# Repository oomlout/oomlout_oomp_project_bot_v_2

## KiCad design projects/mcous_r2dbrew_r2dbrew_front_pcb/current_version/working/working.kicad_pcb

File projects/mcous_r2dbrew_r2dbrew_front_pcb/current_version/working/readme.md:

# r2dbrew
 
## summary 
* id: mcous_r2dbrew_r2dbrew_front_pcb
* user: mcous
* name: r2dbrew
* board: r2dbrew_front_pcb
* repo: https://github.com/mcous/r2dbrew
* src_file_repo_kicad_pcb: pcb/r2dbrew-front-pcb/r2dbrew-front-pcb.kicad_pcb
* src_file_repo_kicad_pcb_link: https://github.com/mcous/r2dbrew/tree/master/pcb/r2dbrew-front-pcb/r2dbrew-front-pcb.kicad_pcb

* src_file_repo_sch: pcb/r2dbrew-front-pcb/r2dbrew-front-pcb.sch
* src_file_repo_sch_link: https://github.com/mcous/r2dbrew/tree/master/pcb/r2dbrew-front-pcb/r2dbrew-front-pcb.sch
* full details link: https://github.com/oomlout/oomlout_oomp_project_bot_v_2/tree/main/projects/mcous_r2dbrew_r2dbrew_front_pcb/current_version/working

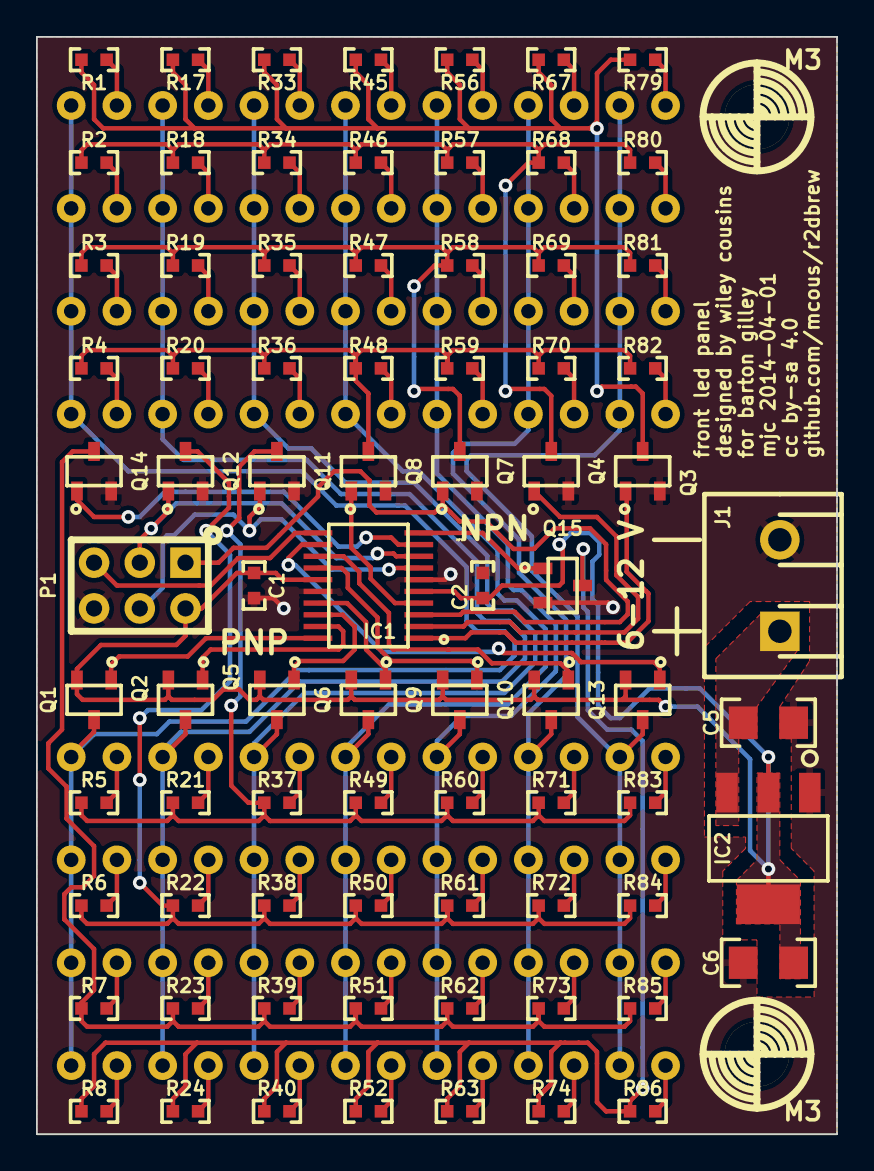
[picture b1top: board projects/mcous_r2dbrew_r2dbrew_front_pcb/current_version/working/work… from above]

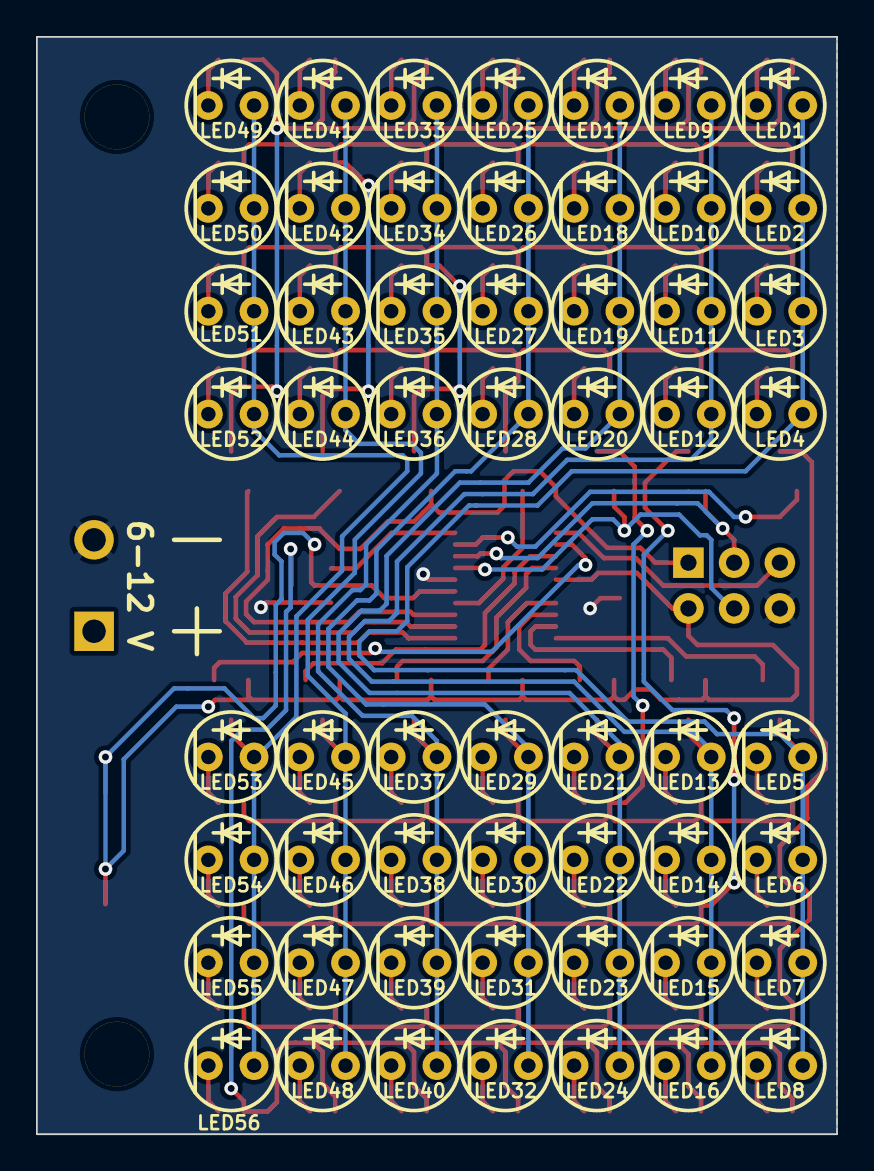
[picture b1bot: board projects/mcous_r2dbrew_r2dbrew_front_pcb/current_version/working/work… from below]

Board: 2 copper layers, 44.5 x 61.0 mm, 137 parts (56 on the bottom side), 90 nets.

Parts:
C1, C2: 0.1uF; 0603(1608m)
C5: 10uF; 1206(3216m)
C6: 22uF; 1206(3216m)
IC1: ATTINY167; TSSOP20
IC2: LM1117; SOT223
J1: 6-12V; 1x2-SCREW-TERM_P200mil
LED1, LED2, LED3, LED4, LED5, LED6, LED7, LED8, LED9, LED10, LED11, LED12, LED13, LED14, LED15, LED16, LED17, LED18, LED19, LED20, LED21, LED22, LED23, LED24, LED25, LED26, LED27, LED28, LED29, LED30, LED31, LED32, LED33, LED34, LED35, LED36, LED37, LED38, LED39, LED40, LED41, LED42, LED43, LED44, LED45, LED46, LED47, LED48, LED49, LED50, LED51, LED52, LED53, LED54, LED55, LED56: LED; 5mm-THRU-LED
M3, M3#2: VAL**; M3
P1: AVR_ISP; 2x3-ARRAY_P100mil
Q1, Q2, Q5, Q6, Q9, Q10, Q13: DDTB113ZC; SOT23
Q3, Q4, Q7, Q8, Q11, Q12, Q14, Q15: DDTD113ZC; SOT23
R1, R2, R3, R4, R5, R6, R7, R8, R17, R18, R19, R20, R21, R22, R23, R24, R33, R34, R35, R36, R37, R38, R39, R40, R45, R46, R47, R48, R49, R50, R51, R52, R56, R57, R58, R59, R60, R61, R62, R63, R67, R68, R69, R70, R71, R72, R73, R74, R79, R80, R81, R82, R83, R84, R85, R86: 68Ω; 0603(1608m)

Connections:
/AVR_RST: IC1.11, P1.5
/beer2d2 front LED panel/AVR_C0: IC1.20, Q1.1
/beer2d2 front LED panel/AVR_C1: IC1.19, Q2.1
/beer2d2 front LED panel/AVR_C2: IC1.18, Q5.1
/beer2d2 front LED panel/AVR_C3: IC1.17, Q6.1
/beer2d2 front LED panel/AVR_C4: IC1.14, Q9.1
/beer2d2 front LED panel/AVR_C5: IC1.13, Q10.1
/beer2d2 front LED panel/AVR_C6: IC1.12, Q13.1
/beer2d2 front LED panel/AVR_R0: IC1.1, Q3.1
/beer2d2 front LED panel/AVR_R1: IC1.2, Q4.1
/beer2d2 front LED panel/AVR_R2: IC1.3, P1.1, Q7.1
/beer2d2 front LED panel/AVR_R3: IC1.4, Q8.1
/beer2d2 front LED panel/AVR_R4: IC1.7, P1.4, Q11.1
/beer2d2 front LED panel/AVR_R5: IC1.8, P1.3, Q12.1
/beer2d2 front LED panel/AVR_R6: IC1.9, Q14.1
/beer2d2 front LED panel/AVR_R7: IC1.10, Q15.1
/beer2d2 front LED panel/COL0: LED1.2, LED2.2, LED3.2, LED4.2, LED5.2, LED6.2, LED7.2, LED8.2, Q1.3
/beer2d2 front LED panel/COL1: LED9.2, LED10.2, LED11.2, LED12.2, LED13.2, LED14.2, LED15.2, LED16.2, Q2.3
/beer2d2 front LED panel/COL2: LED17.2, LED18.2, LED19.2, LED20.2, LED21.2, LED22.2, LED23.2, LED24.2, Q5.3
/beer2d2 front LED panel/COL3: LED25.2, LED26.2, LED27.2, LED28.2, LED29.2, LED30.2, LED31.2, LED32.2, Q6.3
/beer2d2 front LED panel/COL4: LED33.2, LED34.2, LED35.2, LED36.2, LED37.2, LED38.2, LED39.2, LED40.2, Q9.3
/beer2d2 front LED panel/COL5: LED41.2, LED42.2, LED43.2, LED44.2, LED45.2, LED46.2, LED47.2, LED48.2, Q10.3
/beer2d2 front LED panel/COL6: LED49.2, LED50.2, LED51.2, LED52.2, LED53.2, LED54.2, LED55.2, LED56.2, Q13.3
/beer2d2 front LED panel/ROW0: Q3.3, R1.2, R17.2, R33.2, R45.2, R56.2, R67.2, R79.2
/beer2d2 front LED panel/ROW1: Q4.3, R2.2, R18.2, R34.2, R46.2, R57.2, R68.2, R80.2
/beer2d2 front LED panel/ROW2: Q7.3, R3.2, R19.2, R35.2, R47.2, R58.2, R69.2, R81.2
/beer2d2 front LED panel/ROW3: Q8.3, R4.2, R20.2, R36.2, R48.2, R59.2, R70.2, R82.2
/beer2d2 front LED panel/ROW4: Q11.3, R5.2, R21.2, R37.2, R49.2, R60.2, R71.2, R83.2
/beer2d2 front LED panel/ROW5: Q12.3, R6.2, R22.2, R38.2, R50.2, R61.2, R72.2, R84.2
/beer2d2 front LED panel/ROW6: Q14.3, R7.2, R23.2, R39.2, R51.2, R62.2, R73.2, R85.2
/beer2d2 front LED panel/ROW7: Q15.3, R8.2, R24.2, R40.2, R52.2, R63.2, R74.2, R86.2
GND: C1.1, C2.1, C5.2, C6.2, IC1.6, IC1.16, IC2.1, J1.2, P1.6, Q3.2, Q4.2, Q7.2, Q8.2, Q11.2, Q12.2, Q14.2, Q15.2
unnamed: C5.1, IC2.3, J1.1
unnamed: LED1.1, R1.1
unnamed: LED2.1, R2.1
unnamed: LED3.1, R3.1
unnamed: LED4.1, R4.1
unnamed: LED5.1, R5.1
unnamed: LED6.1, R6.1
unnamed: LED7.1, R7.1
unnamed: LED8.1, R8.1
unnamed: LED9.1, R17.1
unnamed: LED10.1, R18.1
unnamed: LED11.1, R19.1
unnamed: LED12.1, R20.1
unnamed: LED13.1, R21.1
unnamed: LED14.1, R22.1
unnamed: LED15.1, R23.1
unnamed: LED16.1, R24.1
unnamed: LED17.1, R33.1
unnamed: LED18.1, R34.1
unnamed: LED19.1, R35.1
unnamed: LED20.1, R36.1
unnamed: LED21.1, R37.1
unnamed: LED22.1, R38.1
unnamed: LED23.1, R39.1
unnamed: LED24.1, R40.1
unnamed: LED25.1, R45.1
unnamed: LED26.1, R46.1
unnamed: LED27.1, R47.1
unnamed: LED28.1, R48.1
unnamed: LED29.1, R49.1
unnamed: LED30.1, R50.1
unnamed: LED31.1, R51.1
unnamed: LED32.1, R52.1
unnamed: LED33.1, R56.1
unnamed: LED34.1, R57.1
unnamed: LED35.1, R58.1
unnamed: LED36.1, R59.1
unnamed: LED37.1, R60.1
unnamed: LED38.1, R61.1
unnamed: LED39.1, R62.1
unnamed: LED40.1, R63.1
unnamed: LED41.1, R67.1
unnamed: LED42.1, R68.1
unnamed: LED43.1, R69.1
unnamed: LED44.1, R70.1
unnamed: LED45.1, R71.1
unnamed: LED46.1, R72.1
unnamed: LED47.1, R73.1
unnamed: LED48.1, R74.1
unnamed: LED49.1, R79.1
unnamed: LED50.1, R80.1
unnamed: LED51.1, R81.1
unnamed: LED52.1, R82.1
unnamed: LED53.1, R83.1
unnamed: LED54.1, R84.1
unnamed: LED55.1, R85.1
unnamed: LED56.1, R86.1
VCC: C1.2, C2.2, C6.1, IC1.5, IC1.15, IC2.0, IC2.2, P1.2, Q1.2, Q2.2, Q5.2, Q6.2, Q9.2, Q10.2, Q13.2

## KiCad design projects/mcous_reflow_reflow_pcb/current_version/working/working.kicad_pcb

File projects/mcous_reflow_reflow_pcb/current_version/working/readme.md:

# reflow
 
## summary 
* id: mcous_reflow_reflow_pcb
* user: mcous
* name: reflow
* board: reflow_pcb
* repo: https://github.com/mcous/reflow
* src_file_repo_kicad_pcb: pcb/reflow-pcb.kicad_pcb
* src_file_repo_kicad_pcb_link: https://github.com/mcous/reflow/tree/master/pcb/reflow-pcb.kicad_pcb

* src_file_repo_sch: pcb/reflow-pcb.sch
* src_file_repo_sch_link: https://github.com/mcous/reflow/tree/master/pcb/reflow-pcb.sch
* full details link: https://github.com/oomlout/oomlout_oomp_project_bot_v_2/tree/main/projects/mcous_reflow_reflow_pcb/current_version/working

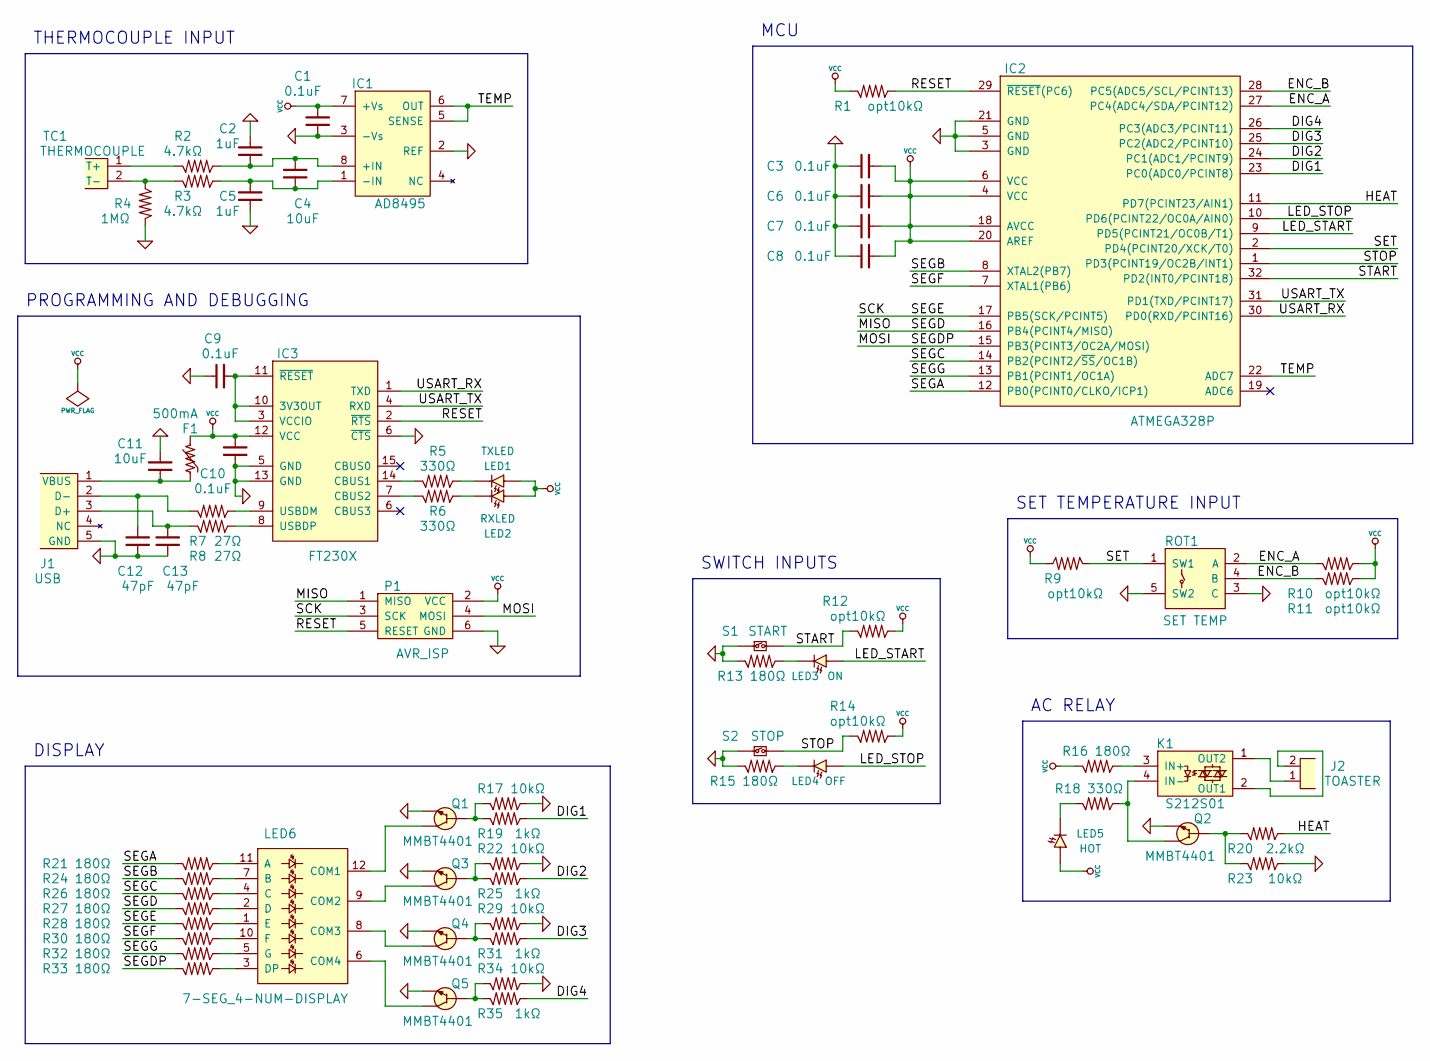
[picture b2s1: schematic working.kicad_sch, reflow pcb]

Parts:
C1, C3, C6, C7, C8, C9, C10: 0.1uF; 0603(1608m)
C2, C5: 1uF; 0603(1608m)
C4, C11: 10uF; 0603(1608m)
C12, C13: 47pF; 0603(1608m)
F1: 500mA; 1206(3216m); Part 0ZCJ0050FF2G
IC1: AD8495; MSOP8; Part AD8495ARMZ
IC2: ATMEGA328P; TQFP32_7mm; Part ATMEGA328P-AU
IC3: FT230X; SSOP16; Part FT230XS-R
J1: USB; MICROUSB_sm; Part 10118192-0001LF
J2: TOASTER; 2-PIN_SCREW-TERM_P200MIL; Part OSTTC022162
K1: S212S01; SHARP_SIP_SSR; Part S212S01F
LED1: TXLED; 0603(1608m)_led
LED2: RXLED; 0603(1608m)_led
LED3: ON; LED-5mm
LED4: OFF; LED-5mm
LED5: HOT; LED-5mm
LED6: 7-SEG_4-NUM-DISPLAY; SF_4-DIGIT_7-SEGMENT_CC; Part COM-11405
P1: AVR_ISP; 2x3-array
Q1, Q2, Q3, Q4, Q5: MMBT4401; SOT23; Part MMBT4401LT1G
R1, R9, R10, R11, R12, R14: opt10kΩ; 0603(1608m)
R2, R3: 4.7kΩ; 0603(1608m)
R4: 1MΩ; 0603(1608m)
R5, R6, R18: 330Ω; 0603(1608m)
R7, R8: 27Ω; 0603(1608m)
R13, R15, R16, R21, R24, R26, R27, R28, R30, R32, R33: 180Ω; 0603(1608m)
R17, R22, R23, R29, R34: 10kΩ; 0603(1608m)
R19, R25, R31, R35: 1kΩ; 0603(1608m)
R20: 2.2kΩ; 0603(1608m)
ROT1: SET TEMP; SF_ROTARY-ENCODER; Part RE130F-41-175F-12P
S1: START; SPST_4-pin-thru
S2: STOP; SPST_4-pin-thru
TC1: THERMOCOUPLE; THERMOCOUPLE_MINI_PCC-SMP; Part PCC-SMP-K

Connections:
/DIG1: IC2.23 (PC0(ADC0/PCINT8)), R19.2
/DIG2: IC2.24 (PC1(ADC1/PCINT9)), R25.2
/DIG3: IC2.25 (PC2(ADC2/PCINT10)), R31.2
/DIG4: IC2.26 (PC3(ADC3/PCINT11)), R35.2
/ENC_A: IC2.27 (PC4(ADC4/SDA/PCINT12)), R10.1, ROT1.2 (A)
/ENC_B: IC2.28 (PC5(ADC5/SCL/PCINT13)), R11.1, ROT1.4 (B)
/HEAT: IC2.11 (PD7(PCINT23/AIN1)), R20.2
/LED_START: IC2.9 (PD5(PCINT21/OC0B/T1)), LED3.2 (A)
/LED_STOP: IC2.10 (PD6(PCINT22/OC0A/AIN0)), LED4.2 (A)
/MISO: IC2.16 (PB4(PCINT4/MISO)), P1.1 (MISO), R27.1
/MOSI: IC2.15 (PB3(PCINT3/OC2A/MOSI)), P1.4 (MOSI), R33.1
/RESET: IC2.29 (~RESET(PC6)), IC3.2 (~RTS), P1.5 (RESET), R1.2
/SCK: IC2.17 (PB5(SCK/PCINT5)), P1.3 (SCK), R28.1
/SEGA: IC2.12 (PB0(PCINT0/CLKO/ICP1)), R21.1
/SEGB: IC2.8 (XTAL2(PB7)), R24.1
/SEGC: IC2.14 (PB2(PCINT2/~SS/OC1B)), R26.1
/SEGF: IC2.7 (XTAL1(PB6)), R30.1
/SEGG: IC2.13 (PB1(PCINT1/OC1A)), R32.1
/SET: IC2.2 (PD4(PCINT20/XCK/T0)), R9.1, ROT1.1 (SW1)
/START: IC2.32 (PD2(INT0/PCINT18)), R12.1, S1.2
/STOP: IC2.1 (PD3(PCINT19/OC2B/INT1)), R14.1, S2.2
/TEMP: IC1.5 (SENSE), IC1.6 (OUT), IC2.22 (ADC7)
/USART_RX: IC2.30 (PD0(RXD/PCINT16)), IC3.1 (TXD)
/USART_TX: IC2.31 (PD1(TXD/PCINT17)), IC3.4 (RXD)
GND: C1.1, C2.2, C3.1, C5.1, C6.1, C7.1, C8.1, C9.1, C10.1, C11.2, C12.1, C13.1, IC1.2 (REF), IC1.3 (-Vs), IC2.3 (GND), IC2.5 (GND), IC2.21 (GND), IC3.5 (GND), IC3.6 (CBUS3), IC3.13 (GND), J1.5 (GND), P1.6 (GND), Q1.2 (E), Q2.2 (E), Q3.2 (E), Q4.2 (E), Q5.2 (E), R4.1, R13.1, R15.1, R17.2, R22.2, R23.2, R29.2, R34.2, ROT1.3 (C), ROT1.5 (SW2), S1.1, S2.1; also elsewhere on the board
unnamed: LED6.11 (A), R21.2
unnamed: LED3.1 (C), R13.2
unnamed: LED4.1 (C), R15.2
unnamed: LED6.7 (B), R24.2
unnamed: LED6.4 (C), R26.2
unnamed: LED6.2 (D), R27.2
unnamed: LED6.1 (E), R28.2
unnamed: LED6.10 (F), R30.2
unnamed: LED6.5 (G), R32.2
unnamed: LED6.3 (DP), R33.2
unnamed: Q1.1 (B), R17.1, R19.1
unnamed: K1.3 (IN+), R16.2
unnamed: Q4.1 (B), R29.1, R31.1
unnamed: Q5.1 (B), R34.1, R35.1
unnamed: LED6.12 (COM1), Q1.3 (C)
unnamed: LED6.9 (COM2), Q3.3 (C)
unnamed: Q3.1 (B), R22.1, R25.1
unnamed: IC3.14 (CBUS1), R5.1
unnamed: IC3.7 (CBUS2), R6.1
unnamed: LED2.1 (C), R6.2
unnamed: IC3.8 (USBDP), R8.2
unnamed: C13.2, J1.3 (D+), R8.1
unnamed: LED1.1 (C), R5.2
unnamed: R2.1, TC1.1 (T+)
unnamed: K1.4 (IN-), Q2.3 (C), R18.2
unnamed: IC3.9 (USBDM), R7.2
unnamed: C9.2, IC3.3 (VCCIO), IC3.10 (3V3OUT), IC3.11 (~RESET)
unnamed: J2.2, K1.2 (OUT1)
unnamed: LED5.1 (C), R18.1
unnamed: J2.1, K1.1 (OUT2)
unnamed: C12.2, J1.2 (D-), R7.1
unnamed: Q2.1 (B), R20.1, R23.1
unnamed: LED6.8 (COM3), Q4.3 (C)
unnamed: LED6.6 (COM4), Q5.3 (C)
unnamed: C2.1, C4.2, IC1.8 (+IN), R2.2
unnamed: R3.1, R4.2, TC1.2 (T-)
unnamed: C4.1, C5.2, IC1.1 (-IN), R3.2
unnamed: C11.1, F1.1, J1.1 (VBUS)
VCC: C1.2, C3.2, C6.2, C7.2, C8.2, C10.2, F1.2, IC1.7 (+Vs), IC2.4 (VCC), IC2.6 (VCC), IC2.18 (AVCC), IC2.20 (AREF), IC3.12 (VCC), LED1.2 (A), LED2.2 (A), LED5.2 (A), P1.2 (VCC), R1.1, R9.2, R10.2, R11.2, R12.2, R14.2, R16.1

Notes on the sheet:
MCU
AC RELAY
SET TEMPERATURE INPUT
SWITCH INPUTS
THERMOCOUPLE INPUT
DISPLAY
PROGRAMMING AND DEBUGGING

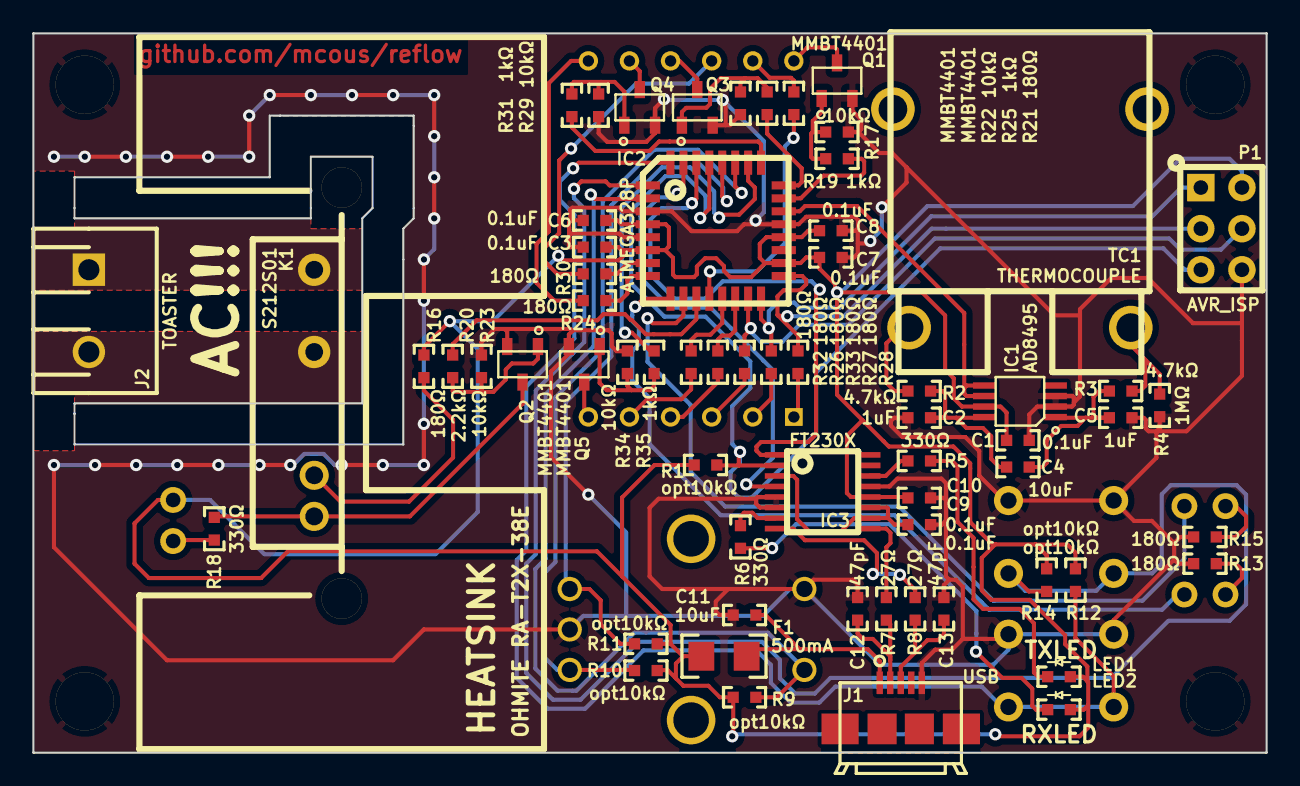
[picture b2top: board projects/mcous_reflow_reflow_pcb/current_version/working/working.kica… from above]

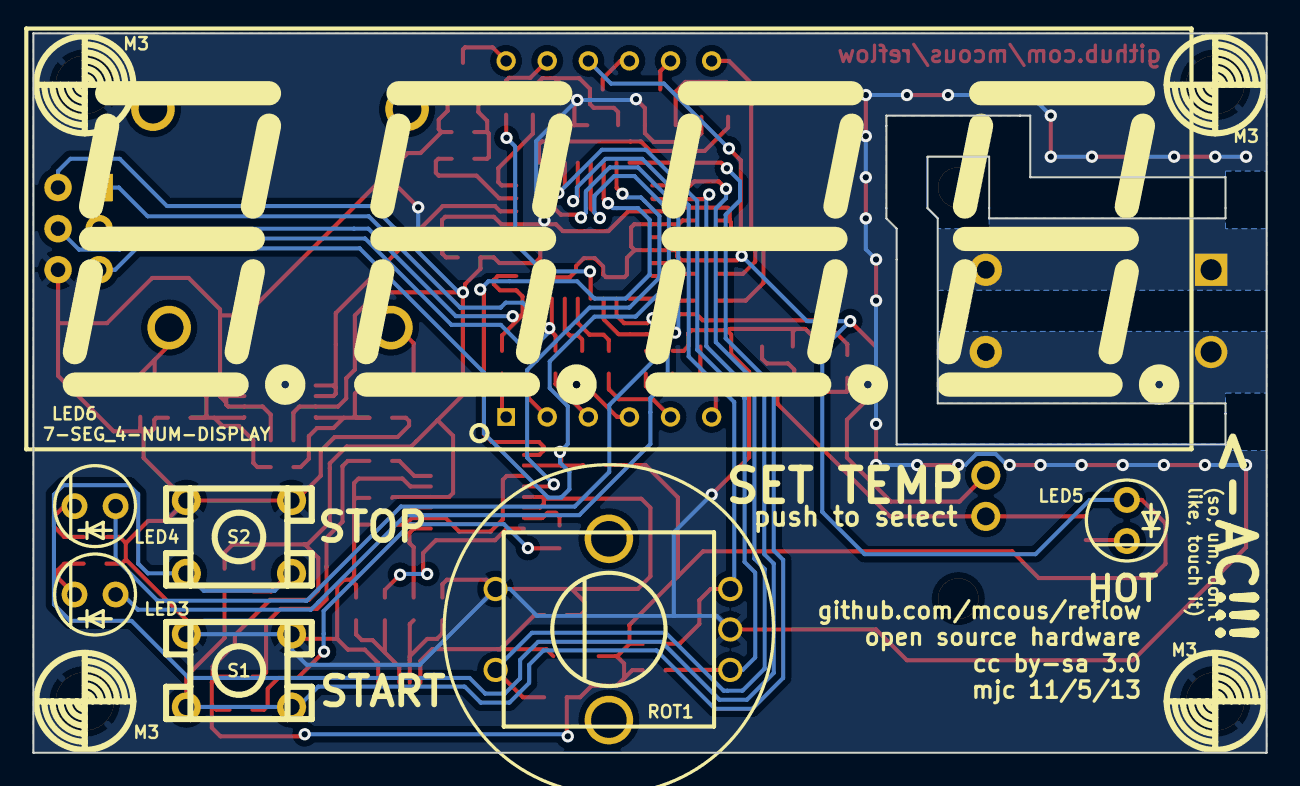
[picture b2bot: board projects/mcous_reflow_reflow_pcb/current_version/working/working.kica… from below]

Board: 2 copper layers, 76.2 x 44.5 mm, 75 parts (11 on the bottom side), 64 nets.

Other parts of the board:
M3, M3#2, M3#3, M3#4: VAL**; M3

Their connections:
GND: M3.1, M3#2.1, M3#3.1, M3#4.1; also elsewhere on the board

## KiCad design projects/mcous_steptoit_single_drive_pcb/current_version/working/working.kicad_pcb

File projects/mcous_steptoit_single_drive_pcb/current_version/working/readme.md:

# steptoit
 
## summary 
* id: mcous_steptoit_single_drive_pcb
* user: mcous
* name: steptoit
* board: single_drive_pcb
* repo: https://github.com/mcous/steptoit
* src_file_repo_kicad_pcb: single-drive_pcb/single-drive_pcb.kicad_pcb
* src_file_repo_kicad_pcb_link: https://github.com/mcous/steptoit/tree/master/single-drive_pcb/single-drive_pcb.kicad_pcb

* src_file_repo_sch: single-drive_pcb/single-drive_pcb.sch
* src_file_repo_sch_link: https://github.com/mcous/steptoit/tree/master/single-drive_pcb/single-drive_pcb.sch
* full details link: https://github.com/oomlout/oomlout_oomp_project_bot_v_2/tree/main/projects/mcous_steptoit_single_drive_pcb/current_version/working

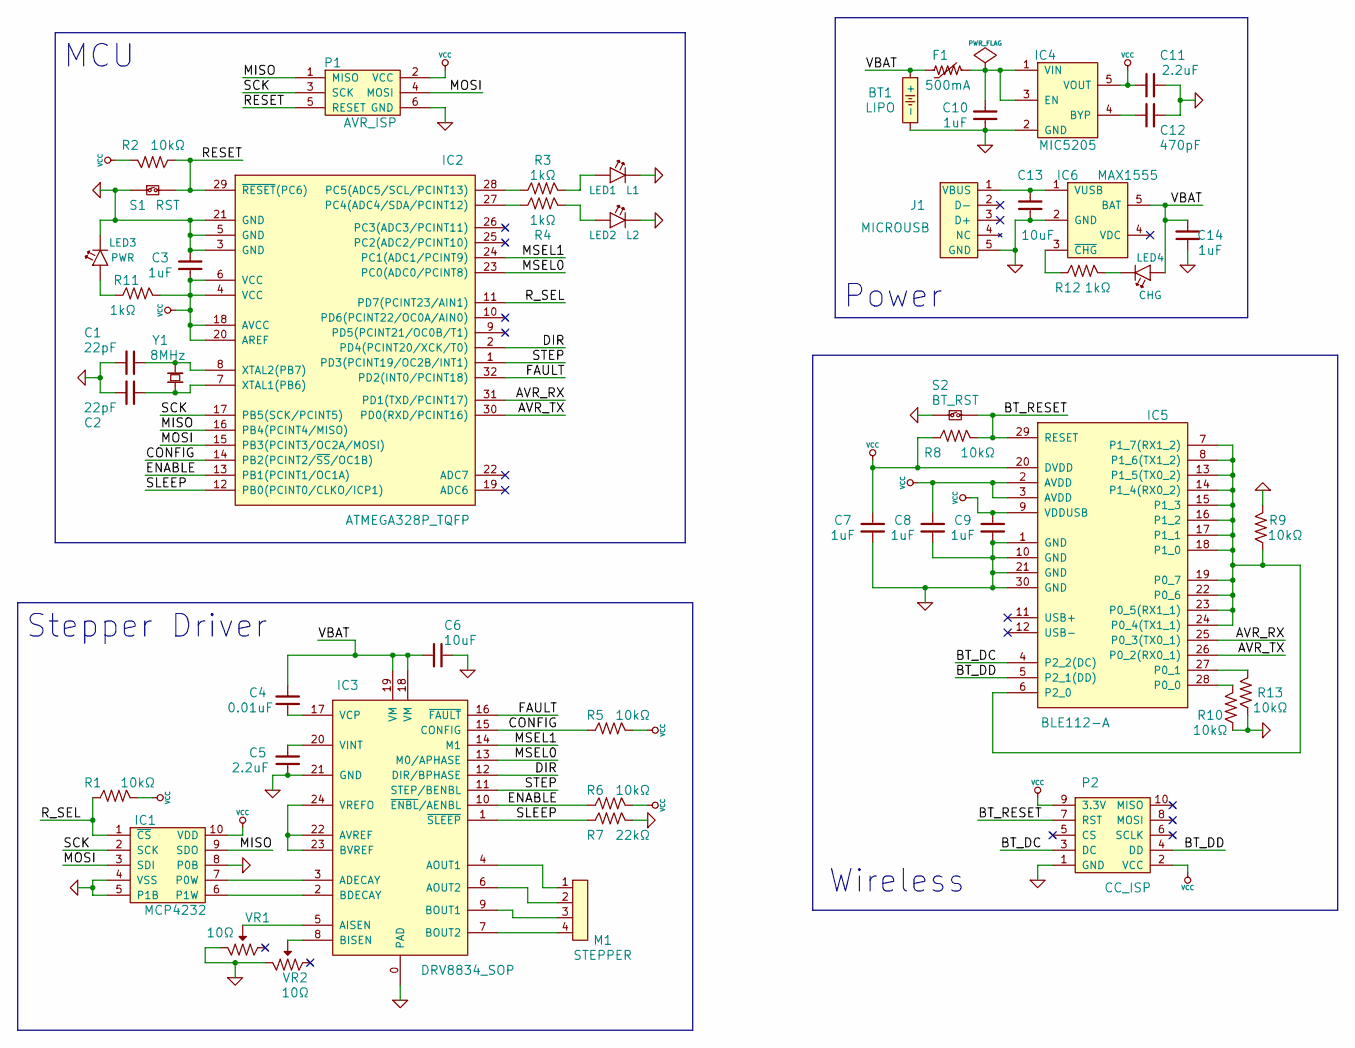
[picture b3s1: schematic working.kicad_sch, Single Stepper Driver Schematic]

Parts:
BT1: LIPO
C1, C2: 22pF
C3, C7, C8, C9, C10, C14: 1uF
C4: 0.01uF
C5, C11: 2.2uF
C6, C13: 10uF
C12: 470pF
F1: 500mA
IC1: MCP4232
IC2: ATMEGA328P_TQFP
IC3: DRV8834_SOP
IC4: MIC5205
IC5: BLE112-A
IC6: MAX1555
J1: MICROUSB
LED1: L1
LED2: L2
LED3: PWR
LED4: CHG
M1: STEPPER
P1: AVR_ISP
P2: CC_ISP
R1, R2, R5, R6, R8, R9, R10, R13: 10kΩ
R3, R4, R11, R12: 1kΩ
R7: 22kΩ
S1: RST
S2: BT_RST
VR1, VR2: 10Ω
Y1: 8MHz

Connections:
/AVR_RX: IC2.31 (PD1(TXD/PCINT17)), IC5.25 (P0_3(TX0_1))
/AVR_TX: IC2.30 (PD0(RXD/PCINT16)), IC5.26 (P0_2(RX0_1))
/BT_DC: IC5.4 (P2_2(DC)), P2.3 (DC)
/BT_DD: IC5.5 (P2_1(DD)), P2.4 (DD)
/BT_RESET: IC5.29 (RESET), P2.7 (RST), R8.2, S2.2
/CONFIG: IC2.14 (PB2(PCINT2/~SS/OC1B)), IC3.15 (CONFIG), R5.1
/DIR: IC2.2 (PD4(PCINT20/XCK/T0)), IC3.12 (DIR/BPHASE)
/ENABLE: IC2.13 (PB1(PCINT1/OC1A)), IC3.10 (~ENBL/AENBL), R6.1
/FAULT: IC2.32 (PD2(INT0/PCINT18)), IC3.16 (~FAULT)
/MISO: IC1.9 (SDO), IC2.16 (PB4(PCINT4/MISO)), P1.1 (MISO)
/MOSI: IC1.3 (SDI), IC2.15 (PB3(PCINT3/OC2A/MOSI)), P1.4 (MOSI)
/MSEL0: IC2.23 (PC0(ADC0/PCINT8)), IC3.13 (M0/APHASE)
/MSEL1: IC2.24 (PC1(ADC1/PCINT9)), IC3.14 (M1)
/RESET: IC2.29 (~RESET(PC6)), P1.5 (RESET), R2.1, S1.2
/R_SEL: IC1.1 (~CS), IC2.11 (PD7(PCINT23/AIN1)), R1.1
/SCK: IC1.2 (SCK), IC2.17 (PB5(SCK/PCINT5)), P1.3 (SCK)
/SLEEP: IC2.12 (PB0(PCINT0/CLKO/ICP1)), IC3.1 (~SLEEP), R7.1
/STEP: IC2.1 (PD3(PCINT19/OC2B/INT1)), IC3.11 (STEP/BENBL)
/VBAT: BT1.1 (+), C4.1, C6.1, C14.2, F1.1, IC3.18 (VM), IC3.19 (VM), IC6.5 (BAT), LED4.2 (A)
GND: BT1.2 (-), C1.2, C2.1, C3.2, C5.1, C6.2, C7.1, C8.1, C9.1, C10.1, C11.2, C12.2, C13.1, C14.1, IC1.4 (VSS), IC1.5 (P1B), IC1.8 (P0B), IC2.3 (GND), IC2.5 (GND), IC2.21 (GND), IC3.0 (PAD), IC3.21 (GND), IC4.2 (GND), IC5.1 (GND), IC5.10 (GND), IC5.21 (GND), IC5.30 (GND), IC6.2 (GND), J1.5 (GND), LED1.1 (C), LED2.1 (C), LED3.1 (C), P1.6 (GND), P2.1 (GND), R7.2, R9.2, R10.1, R13.1, S1.1, S2.1, VR1.3 (E2), VR2.3 (E2)
unnamed: LED4.1 (C), R12.2
unnamed: C13.2, IC6.1 (VUSB), J1.1 (VBUS)
unnamed: IC3.7 (BOUT2), M1.4
unnamed: C10.2, F1.2, IC4.1 (VIN), IC4.3 (EN)
unnamed: LED3.2 (A), R11.1
unnamed: IC3.22 (AVREF), IC3.23 (BVREF), IC3.24 (VREFO)
unnamed: IC6.3 (~CHG), R12.1
unnamed: C4.2, IC3.17 (VCP)
unnamed: C5.2, IC3.20 (VINT)
unnamed: IC3.9 (BOUT1), M1.3
unnamed: IC3.4 (AOUT1), M1.1
unnamed: C12.1, IC4.4 (BYP)
unnamed: IC5.27 (P0_1), R13.2
unnamed: IC3.6 (AOUT2), M1.2
unnamed: IC5.28 (P0_0), R10.2
unnamed: IC1.7 (P0W), IC3.3 (ADECAY)
unnamed: IC1.6 (P1W), IC3.2 (BDECAY)
unnamed: IC3.5 (AISEN), VR1.2 (W)
unnamed: IC3.8 (BISEN), VR2.2 (W)
unnamed: IC2.28 (PC5(ADC5/SCL/PCINT13)), R3.1
unnamed: IC2.27 (PC4(ADC4/SDA/PCINT12)), R4.1
unnamed: LED2.2 (A), R4.2
unnamed: LED1.2 (A), R3.2
unnamed: IC5.6 (P2_0), IC5.7 (P1_7(RX1_2)), IC5.8 (P1_6(TX1_2)), IC5.13 (P1_5(TX0_2)), IC5.14 (P1_4(RX0_2)), IC5.15 (P1_3), IC5.16 (P1_2), IC5.17 (P1_1), IC5.18 (P1_0), IC5.19 (P0_7), IC5.22 (P0_6), IC5.23 (P0_5(RX1_1)), IC5.24 (P0_4(TX1_1)), R9.1
unnamed: C1.1, IC2.8 (XTAL2(PB7)), Y1.2
unnamed: C2.2, IC2.7 (XTAL1(PB6)), Y1.1
VCC: C3.1, C7.2, C8.2, C9.2, C11.1, IC1.10 (VDD), IC2.4 (VCC), IC2.6 (VCC), IC2.18 (AVCC), IC2.20 (AREF), IC4.5 (VOUT), IC5.2 (AVDD), IC5.3 (AVDD), IC5.9 (VDDUSB), IC5.20 (DVDD), P1.2 (VCC), P2.2 (VCC), P2.9 (3.3V), R1.2, R2.2, R5.2, R6.2, R8.1, R11.2

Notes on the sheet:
Wireless
Power
Stepper Driver
MCU

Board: 2 copper layers, 48 parts (0 on the bottom side), 47 nets, no tracks yet.

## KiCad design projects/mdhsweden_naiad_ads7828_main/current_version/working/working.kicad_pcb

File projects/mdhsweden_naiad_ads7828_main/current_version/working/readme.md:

# naiad_ads7828
 
## summary 
* id: mdhsweden_naiad_ads7828_main
* user: mdhsweden
* name: naiad_ads7828
* board: main
* repo: https://github.com/MDHSweden/NAIAD-ADS7828
* src_file_repo_kicad_pcb: LPKF/main.kicad_pcb
* src_file_repo_kicad_pcb_link: https://github.com/MDHSweden/NAIAD-ADS7828/tree/master/LPKF/main.kicad_pcb

* src_file_repo_sch: LPKF/main.sch
* src_file_repo_sch_link: https://github.com/MDHSweden/NAIAD-ADS7828/tree/master/LPKF/main.sch
* full details link: https://github.com/oomlout/oomlout_oomp_project_bot_v_2/tree/main/projects/mdhsweden_naiad_ads7828_main/current_version/working

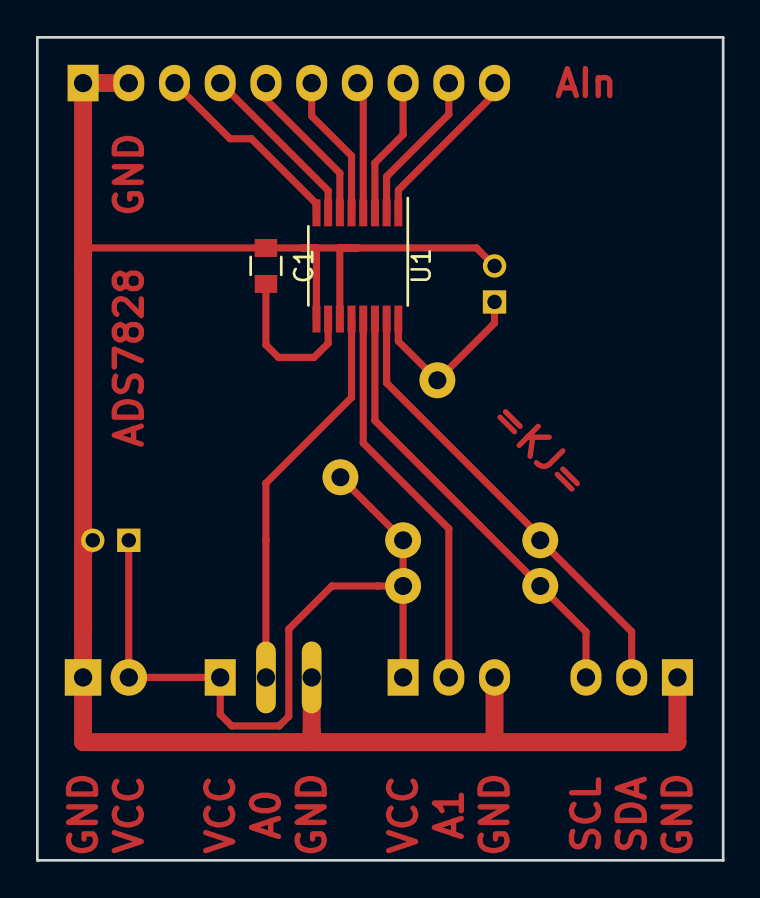
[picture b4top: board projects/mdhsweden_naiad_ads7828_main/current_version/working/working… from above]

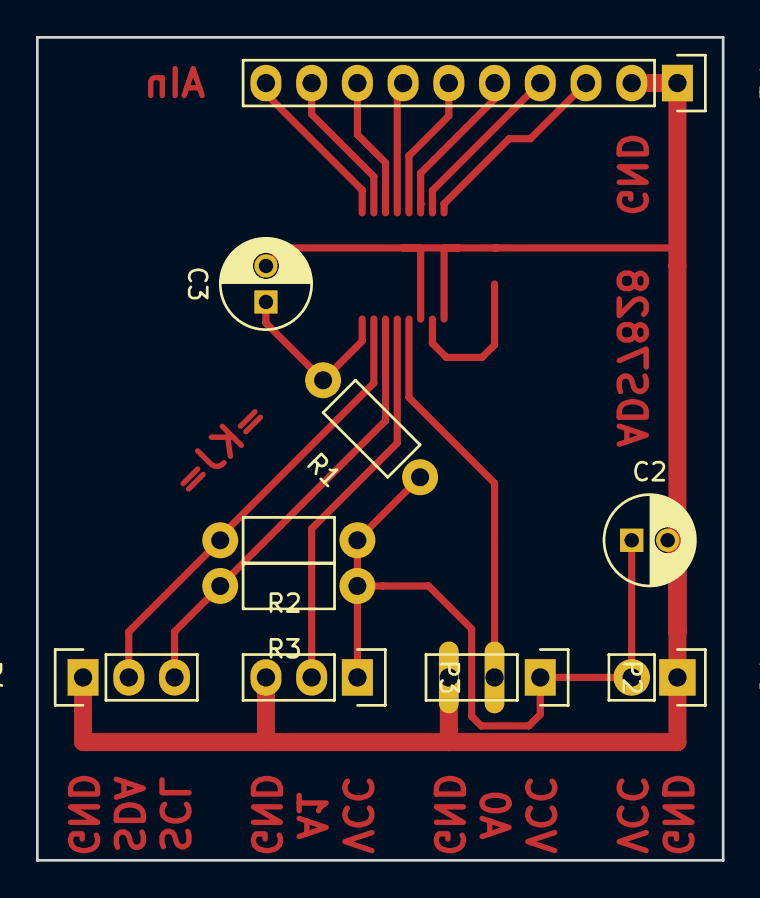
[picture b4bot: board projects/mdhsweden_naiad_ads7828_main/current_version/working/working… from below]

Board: 2 copper layers, 38.1 x 45.7 mm, 12 parts (10 on the bottom side), 16 nets.

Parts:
C1: 0.1u; C_0805
C2, C3: 10u; C_Radial_D5_L11_P2
P1: CONN_01X10; Pin_Header_Straight_1x10
P2: Address 0; Pin_Header_Straight_1x03
P3: Address 1; Pin_Header_Straight_1x03
P4: I2C Connector; Pin_Header_Straight_1x03
P5: Power Connector; Pin_Header_Straight_1x02
R1: 5; Resistor_Horizontal_RM7mm
R2, R3: 2K; Resistor_Horizontal_RM7mm
U1: ADS7828; TSSOP-16_4.4x5mm_Pitch0.65mm

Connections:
/A0: P2.2, U1.12
/A1: P3.2, U1.13
/SCL: P4.3, R3.2, U1.14
/SDA: P4.2, R2.2, U1.15
GND: C1.1, C2.2, C3.2, P1.1, P1.2, P2.3, P3.3, P4.1, P5.1, U1.9, U1.11
unnamed: C1.2, U1.10
unnamed: C3.1, R1.2, U1.16
unnamed: P1.3, U1.8
unnamed: P1.4, U1.7
unnamed: P1.5, U1.6
unnamed: P1.6, U1.5
unnamed: P1.7, U1.4
unnamed: P1.8, U1.3
unnamed: P1.9, U1.2
unnamed: P1.10, U1.1
VCC: C2.1, P2.1, P3.1, P5.2, R1.1, R2.1, R3.1

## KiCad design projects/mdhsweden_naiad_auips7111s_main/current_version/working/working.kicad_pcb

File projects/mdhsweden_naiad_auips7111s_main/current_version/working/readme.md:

# naiad_auips7111s
 
## summary 
* id: mdhsweden_naiad_auips7111s_main
* user: mdhsweden
* name: naiad_auips7111s
* board: main
* repo: https://github.com/MDHSweden/NAIAD-AUIPS7111S
* src_file_repo_kicad_pcb: p3/main.kicad_pcb
* src_file_repo_kicad_pcb_link: https://github.com/MDHSweden/NAIAD-AUIPS7111S/tree/master/p3/main.kicad_pcb

* src_file_repo_sch: p3/main.sch
* src_file_repo_sch_link: https://github.com/MDHSweden/NAIAD-AUIPS7111S/tree/master/p3/main.sch
* full details link: https://github.com/oomlout/oomlout_oomp_project_bot_v_2/tree/main/projects/mdhsweden_naiad_auips7111s_main/current_version/working

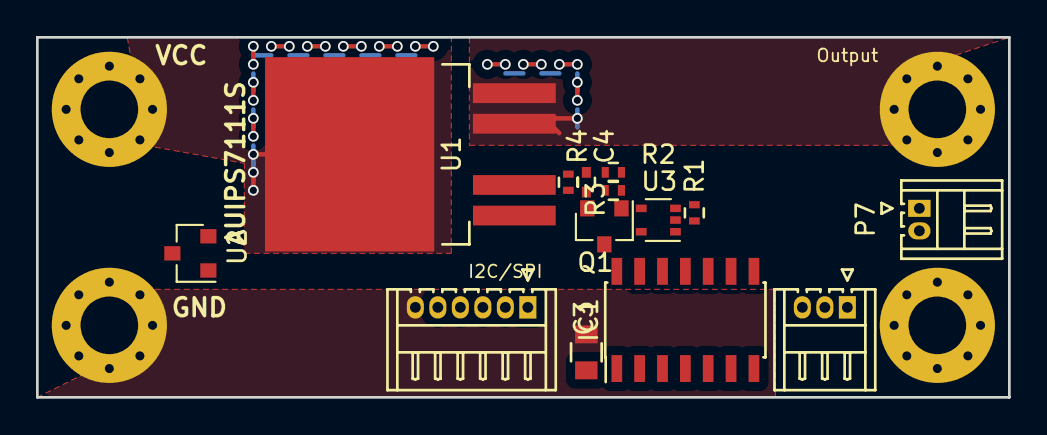
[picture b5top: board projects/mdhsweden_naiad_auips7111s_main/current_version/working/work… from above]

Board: 2 copper layers, 54.0 x 20.0 mm, 18 parts (0 on the bottom side), 15 nets.

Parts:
C3: 10uF; C_0805
C4: 1uF; C_0402
IC1: ATTINY84-S; SOIC-14_3.9x8.7mm_Pitch1.27mm
P1, P4, P5, P6: CONN_01X01; MountingHole_3.2mm_M3_Pad_Via
P2: CONN_01X06; Hirose_DF13-06P-1.25DS_06x1.25mm_Angled
P3: CONN_01X03; Hirose_DF13-03P-1.25DS_03x1.25mm_Angled
P7: CONN_01X02; Hirose_DF13-02P-1.25DS_02x1.25mm_Angled
Q1: BSS138; SOT-23
R1, R2: 4.7k; R_0402
R3: 10k; R_0402
R4: 3.3k; R_0402
U1: AUIPS7111S; TO-263-!3
U2: LM3480-5.0; SOT-23
U3: 74LVC1G08; SOT-353

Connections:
+5V: C3.1, IC1.1, P2.5, P3.2, U2.1, U3.5
/Current_Feedback: IC1.12, R3.1
/ENB1: IC1.10, U3.1
/ENB2: P3.3, R1.1, U3.2
/IN: Q1.3, U1.1
/Ifb: C4.1, R3.2, R4.1, U1.2
/MISO: IC1.8, P2.3
/Out: P5.1, U1.4, U1.5
/PWM1: IC1.5, P7.2
/RESET: IC1.4, P2.2
/SCL/SCK: IC1.9, P2.4
/SDA/MOSI: IC1.7, P2.1
GND: C3.2, C4.2, IC1.14, P2.6, P3.1, P4.1, P6.1, P7.1, Q1.2, R1.2, R2.2, R4.2, U2.3, U3.3
unnamed: Q1.1, R2.1, U3.4
VCC: P1.1, U1.3, U2.2

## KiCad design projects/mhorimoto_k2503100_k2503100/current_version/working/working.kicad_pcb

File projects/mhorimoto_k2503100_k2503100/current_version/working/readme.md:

# k2503100
 
## summary 
* id: mhorimoto_k2503100_k2503100
* user: mhorimoto
* name: k2503100
* board: k2503100
* repo: https://github.com/mhorimoto/k2503100
* src_file_repo_kicad_pcb: KiCAD/k2503100.kicad_pcb
* src_file_repo_kicad_pcb_link: https://github.com/mhorimoto/k2503100/tree/main/KiCAD/k2503100.kicad_pcb
* src_file_repo_kicad_sch: KiCAD/k2503100.kicad_sch
* src_file_repo_kicad_sch_link: https://github.com/mhorimoto/k2503100/tree/main/KiCAD/k2503100.kicad_sch

* src_file_repo_sch: 
* src_file_repo_sch_link: https://github.com/mhorimoto/k2503100/tree/main/
* full details link: https://github.com/oomlout/oomlout_oomp_project_bot_v_2/tree/main/projects/mhorimoto_k2503100_k2503100/current_version/working

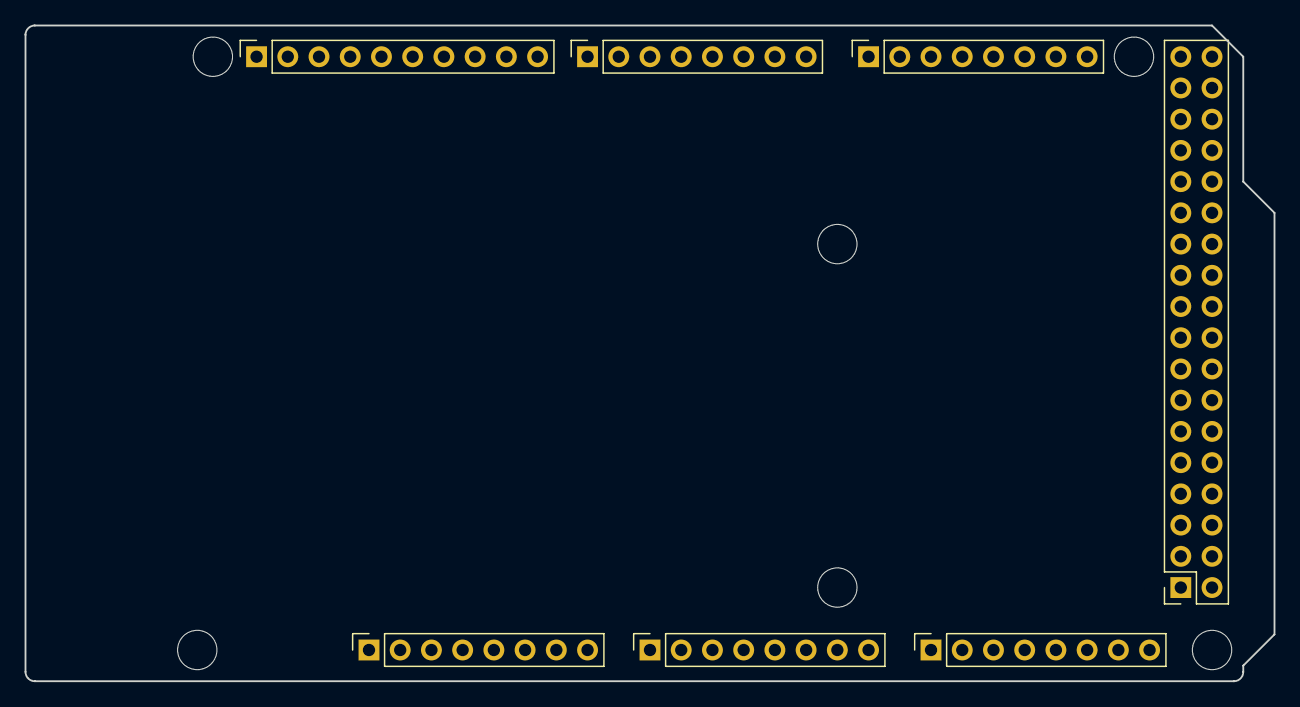
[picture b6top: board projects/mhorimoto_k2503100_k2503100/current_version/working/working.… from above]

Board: 2 copper layers, 101.6 x 53.3 mm, 13 parts (0 on the bottom side), 4 nets, no tracks yet.

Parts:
J1: Power; PinSocket_1x08_P2.54mm_Vertical
J2: PWM; PinSocket_1x10_P2.54mm_Vertical
J3, J5: Analog; PinSocket_1x08_P2.54mm_Vertical
J4: PWM; PinSocket_1x08_P2.54mm_Vertical
J6: Communication; PinSocket_1x08_P2.54mm_Vertical
J7: Digital; PinSocket_2x18_P2.54mm_Vertical
MH1, MH2, MH3, MH4, MH5, MH6: MountingHole_3.2mm

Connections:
+5V: J1.5, J7.35, J7.36
/SCL/21: J2.1, J6.8
/SDA/20: J2.2, J6.7
GND: J1.6, J1.7, J2.4, J7.1, J7.2

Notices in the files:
projects/mcous_r2dbrew_r2dbrew_front_pcb/current_version/working/working.kicad_pcb:
released under the terms of the CC BY-SA 4.0 license
cc by-sa 4.0
projects/mcous_r2dbrew_r2dbrew_front_pcb/current_version/working/working.kicad_sch:
shared under the terms of the Creative Commons Attribution Share-Alike 4.0 license
projects/mcous_reflow_reflow_pcb/current_version/working/working.kicad_pcb:
shared under the terms of the Creative Commons Attribution Share-Alike 3.0 license
cc by-sa 3.0
